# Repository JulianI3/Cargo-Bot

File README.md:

# Cargo-Bot
Repositorio para el proyecto de la materia Taller de Ingeniería Electrónica de la Universidad Nacional de Colombia.

## Integrantes
- Julián David Benítez _jbenitezm@unal.edu.co_
- Julián Ricardo Torres _jutorresz@unal.edu.co_
- Maria Camila Díaz _mdiazar@unal.edu.co_

Taller de Ingeniería Electrónica, grupo 6(1), profesor Jhonny Cubides.

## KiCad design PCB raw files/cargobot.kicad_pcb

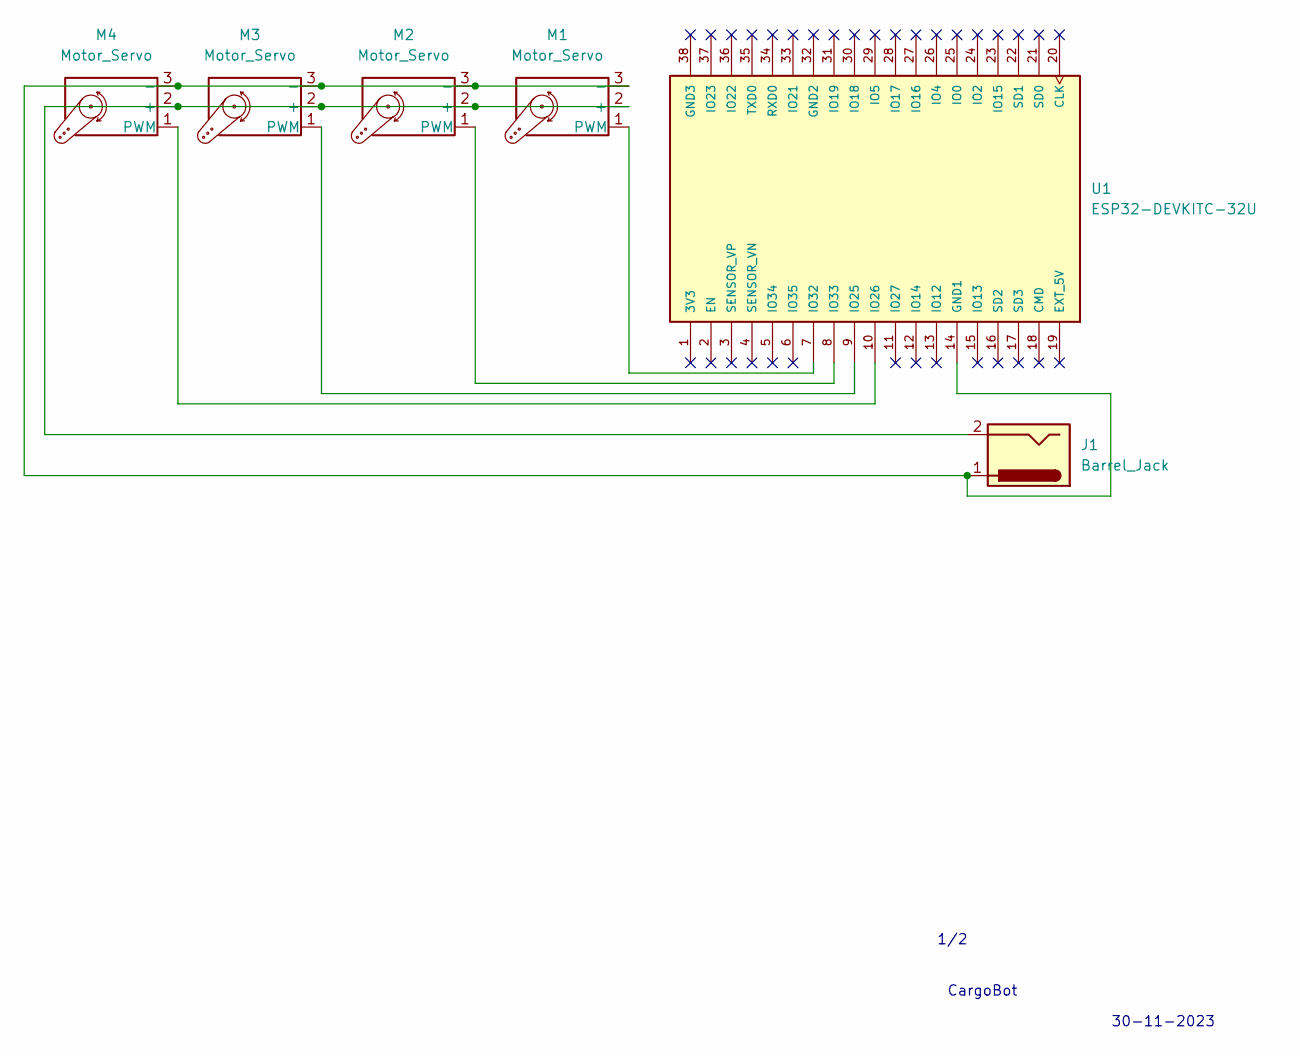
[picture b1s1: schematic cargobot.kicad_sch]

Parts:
J1: Barrel_Jack; PinSocket_1x02_P2.54mm_Vertical
M1, M2, M3, M4: Motor_Servo; PinHeader_1x03_P2.54mm_Vertical
U1: ESP32-DEVKITC-32U; MODULE_ESP32-DEVKITC-32U; PARTREV N/A

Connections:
unnamed: J1.2, M1.2 (+), M2.2 (+), M3.2 (+), M4.2 (+)
unnamed: J1.1, M1.3 (-), M2.3 (-), M3.3 (-), M4.3 (-), U1.14 (GND1)
unnamed: M1.1 (PWM), U1.7 (IO32)
unnamed: M2.1 (PWM), U1.8 (IO33)
unnamed: M3.1 (PWM), U1.9 (IO25)
unnamed: M4.1 (PWM), U1.10 (IO26)

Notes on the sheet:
1/2
CargoBot
30-11-2023

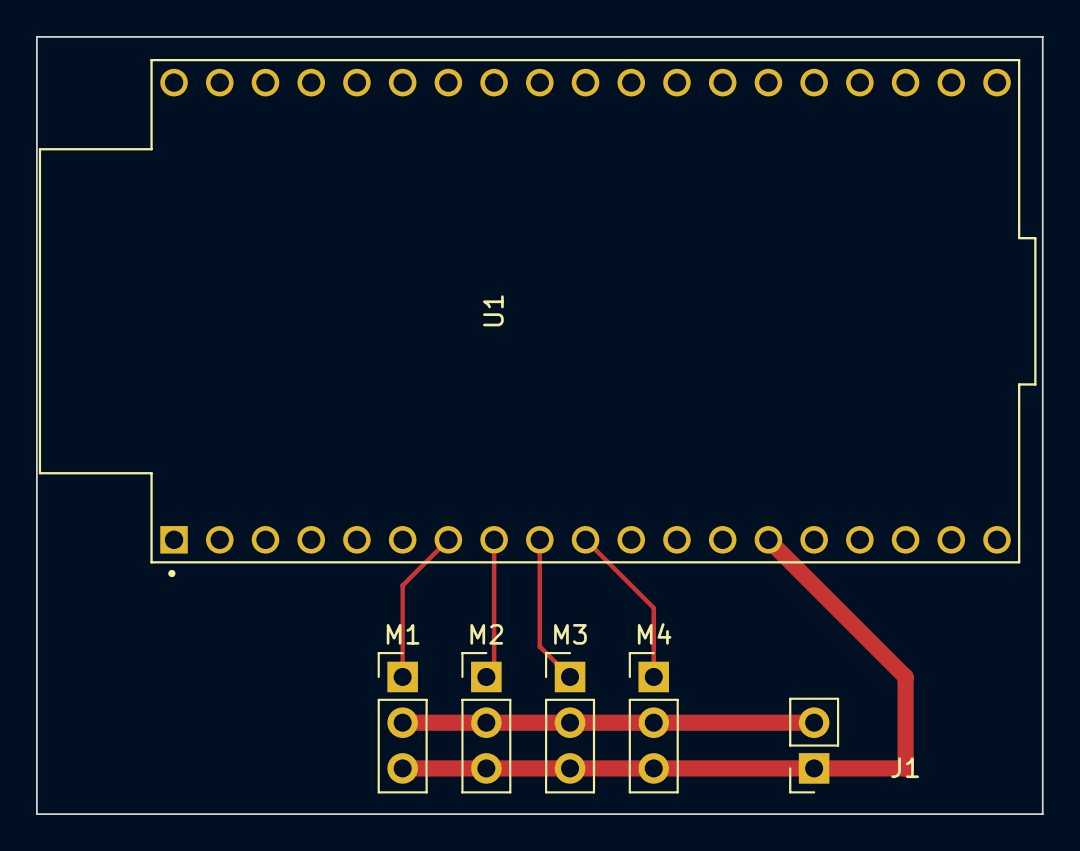
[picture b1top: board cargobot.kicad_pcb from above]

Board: 2 copper layers, 55.9 x 43.2 mm, 6 parts (0 on the bottom side), 6 nets.

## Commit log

2023-10-06 Diagramas
2023-11-22 Subsections
2023-12-01 Create pcb folder
2023-12-01 Create put here the files
2023-12-01 Create here the code
2023-12-01 Create other files
2023-12-01 Create DWG
2023-12-01 Create COSA
2023-12-01 Create COSA1
2023-12-01 Create a
